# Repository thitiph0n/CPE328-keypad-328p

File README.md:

# PEERAPHATR-1669
UART 4X4 Matrix Keypad with Red LED Backlight.

CPE328 Term project

## Our team 👶:
* Chayasit Ingkawaranon
* Thanitnan Phraelai
* Thakorn Krittayakunakorn
* Thitiphon Kengsanguansit
* Peeraphatr Khemachit

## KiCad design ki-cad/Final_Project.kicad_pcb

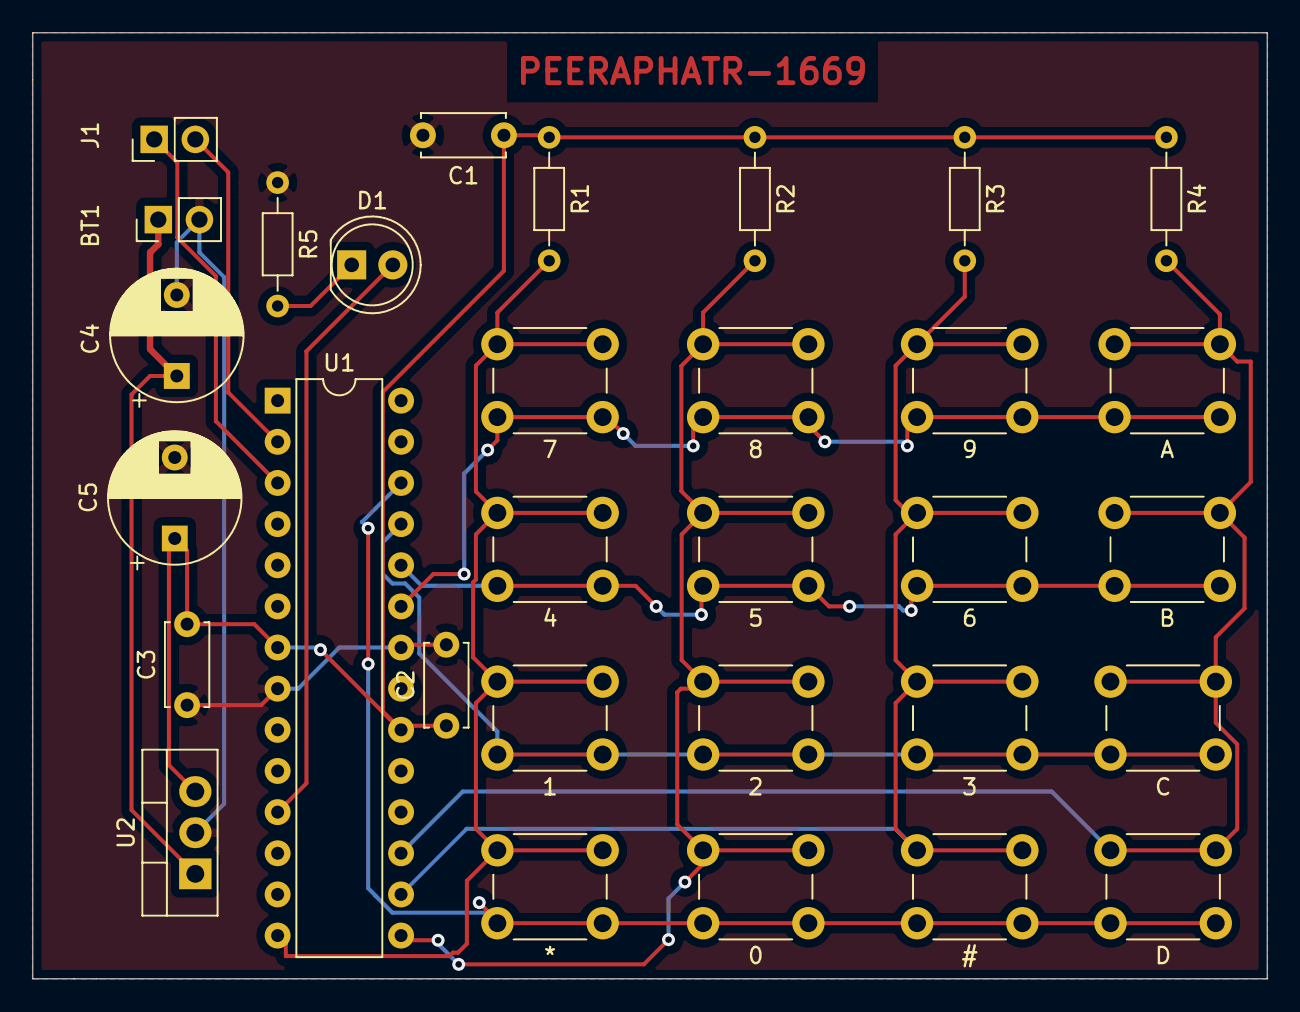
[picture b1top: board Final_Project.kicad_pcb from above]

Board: 2 copper layers, 76.2 x 58.4 mm, 30 parts (0 on the bottom side), 15 nets.

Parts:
0, 1, 2, 3, 4, 5, 6, 7, 8, 9: SW_Push; SW_PUSH_6mm
*: SW_Push; SW_PUSH_6mm
A: SW_Push; SW_PUSH_6mm
B: SW_Push; SW_PUSH_6mm
BT1: +9V; PinHeader_1x02_P2.54mm_Vertical
C: SW_Push; SW_PUSH_6mm
C1, C2, C3: 0.1uF; C_Disc_D5.0mm_W2.5mm_P5.00mm
C4, C5: 100uF; CP_Radial_D8.0mm_P5.00mm
D: SW_Push; SW_PUSH_6mm
D1: LED; LED_D5.0mm
J1: Conn_01x02_Male; PinHeader_1x02_P2.54mm_Vertical
R1, R2, R3, R4: 10K; R_Axial_DIN0204_L3.6mm_D1.6mm_P7.62mm_Horizontal
R5: 330R; R_Axial_DIN0204_L3.6mm_D1.6mm_P7.62mm_Horizontal
U1: ATmega328P-PU; DIP-28_W7.62mm
U2: LM7805_TO220; TO-220-3_Vertical

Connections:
+5V: C1.1, C2.1, C3.2, C5.1, R1.1, R2.1, R3.1, R4.1, U1.7, U1.20, U2.3
GND: BT1.2, C1.2, C2.2, C3.1, C4.2, C5.2, R5.1, U1.8, U1.22, U2.2
unnamed: BT1.1, C4.1, U2.1
unnamed: D1.1, R5.2
unnamed: D1.2, U1.11
unnamed: J1.1, U1.3
unnamed: J1.2, U1.2
unnamed: 1.2, 4.2, 7.2, *.2, R1.2, U1.14
unnamed: 0.2, 2.2, 5.2, 8.2, R2.2, U1.15
unnamed: 3.2, 6.2, 9.2, R3.2, U1.16
unnamed: A.2, B.2, C.2, D.2, R4.2, U1.17
unnamed: 7.1, 8.1, 9.1, A.1, U1.23
unnamed: 4.1, 5.1, 6.1, B.1, U1.24
unnamed: 1.1, 2.1, 3.1, C.1, U1.25
unnamed: 0.1, *.1, D.1, U1.26

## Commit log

2021-05-07 Hai Nong Palm Pai Tum Fai Na
2021-05-07 + Dimming LED function
2021-05-08 add PCB
2021-05-08 Change folder name
2021-05-08 Fix control LED in status mode
2021-05-08 Remove client code
